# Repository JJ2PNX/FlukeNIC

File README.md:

# FlukeNIC - Fluke 884x Web Control & Logger Card

## Overview
The Fluke 884x is an outstanding multimeter.  
Even after 40+ years since its production, most units still function properly and maintain excellent accuracy.  
It's likely more reliable than many cheap modern benchtop meters.  
Its value increases when used in ways unique to benchtop instruments, beyond what handheld meters offer.  
GPIB was the traditional method, but a bit far from modern solution.  
I developed built-in web control and logger card that replaces the original GPIB board.  
NIC ... acronym of Network Interface Card.

---

## Features of This Card
- **WiFi Connectivity**
- **Web-based Control**
- **SD Card Stand-alone Logging**
- **Built-in, No modifications to the main unit required**

---

## How to Get

### 1. Hardware
Currently, no pre-assembled units or kits are available. Please build from the PCB.  
PCB fabrication files (UnitA/B.zip) are for JLCPCB.  
All necessary design materials are in the *hardware* directory.

### 2. Firmware
#### Method 1: Using ESP-IDF

1. Set up the ESP-IDF environment.
2. Clone the repository.
3. Refer to `firmware/README.md` for firmware download instructions.

#### Method 2: Using Flash Download Tool

1. Download **Flash Download Tool** from Espressif.  
   https://docs.espressif.com/projects/esp-test-tools/en/latest/esp32/production_stage/tools/flash_download_tool.html
2. Download `merge.bin` from the `firmware` directory to flash memory at address `0x0`.

---

## Help / How to Use

### 1. WiFi Connection
By default, FlukeNIC operates as a WiFi access point (AP).
- **SSID:** FlukeNIC  
- **Password:** 88408842  
- **IP Address:** 192.168.4.1  

You can configure WiFi Station settings by connecting to this AP, or by using the WPS push-button method.

#### WPS Push-Button Setup

1. Press the **SRQ** button repeatedly until the **SRQ** indicator lights.
2. When WPS succeeds, the **SRQ** indicator turns off and the **LISTEN** indicator turns on.

Settings are saved to flash memory, so the **LISTEN** indicator should light automatically upon the next power-on.

**Fluke Indicator Summary:**
| Indicator | Meaning |
|-----------|---------|
| SRQ | WiFi WPS Request |
| LISTEN | WiFi Associated |
| TALK | Logging is Active |ESP_ERROR_CHECK

---

### 2. Browser Access
Currently, only DHCP-assigned IPs are supported.  
In most cases, you can access it via:
http://flukenic.local/
If that doesn't work, check the DHCP-assigned IP address on your WiFi router.  
If you got the web interface, you probably won’t need further instructions!

---

### 3. Logging
microSD card is required.  
Start/stop operation can be performed using web-control or front panel **LOCAL** button.  
When logging is active, **TALK** indicator lights up.  
Results can be obtained using File Manager menu, or directly from microSD card, But hot swap is not supported.

---

### 4. Configuration
- Be sure to select the correct model (**8840 / 8842**).
- Other settings are optional.
- All configurations are saved to flash memory.

---

### 5. Troubleshooting
Communication with the Fluke unit is based on reverse-engineering and may malfunction with unexpected inputs.  
In such cases, use the **“Last bytes”** function in the Info menu to inspect the last communication log.  
Feel free to contact me — there may be a fix. Contributions are welcome!

---

### 6. Additional Notes
- SD card hot-swapping is not supported.  
Please insert or remove the card only when the power is off.
- BNC output is not implimented now.

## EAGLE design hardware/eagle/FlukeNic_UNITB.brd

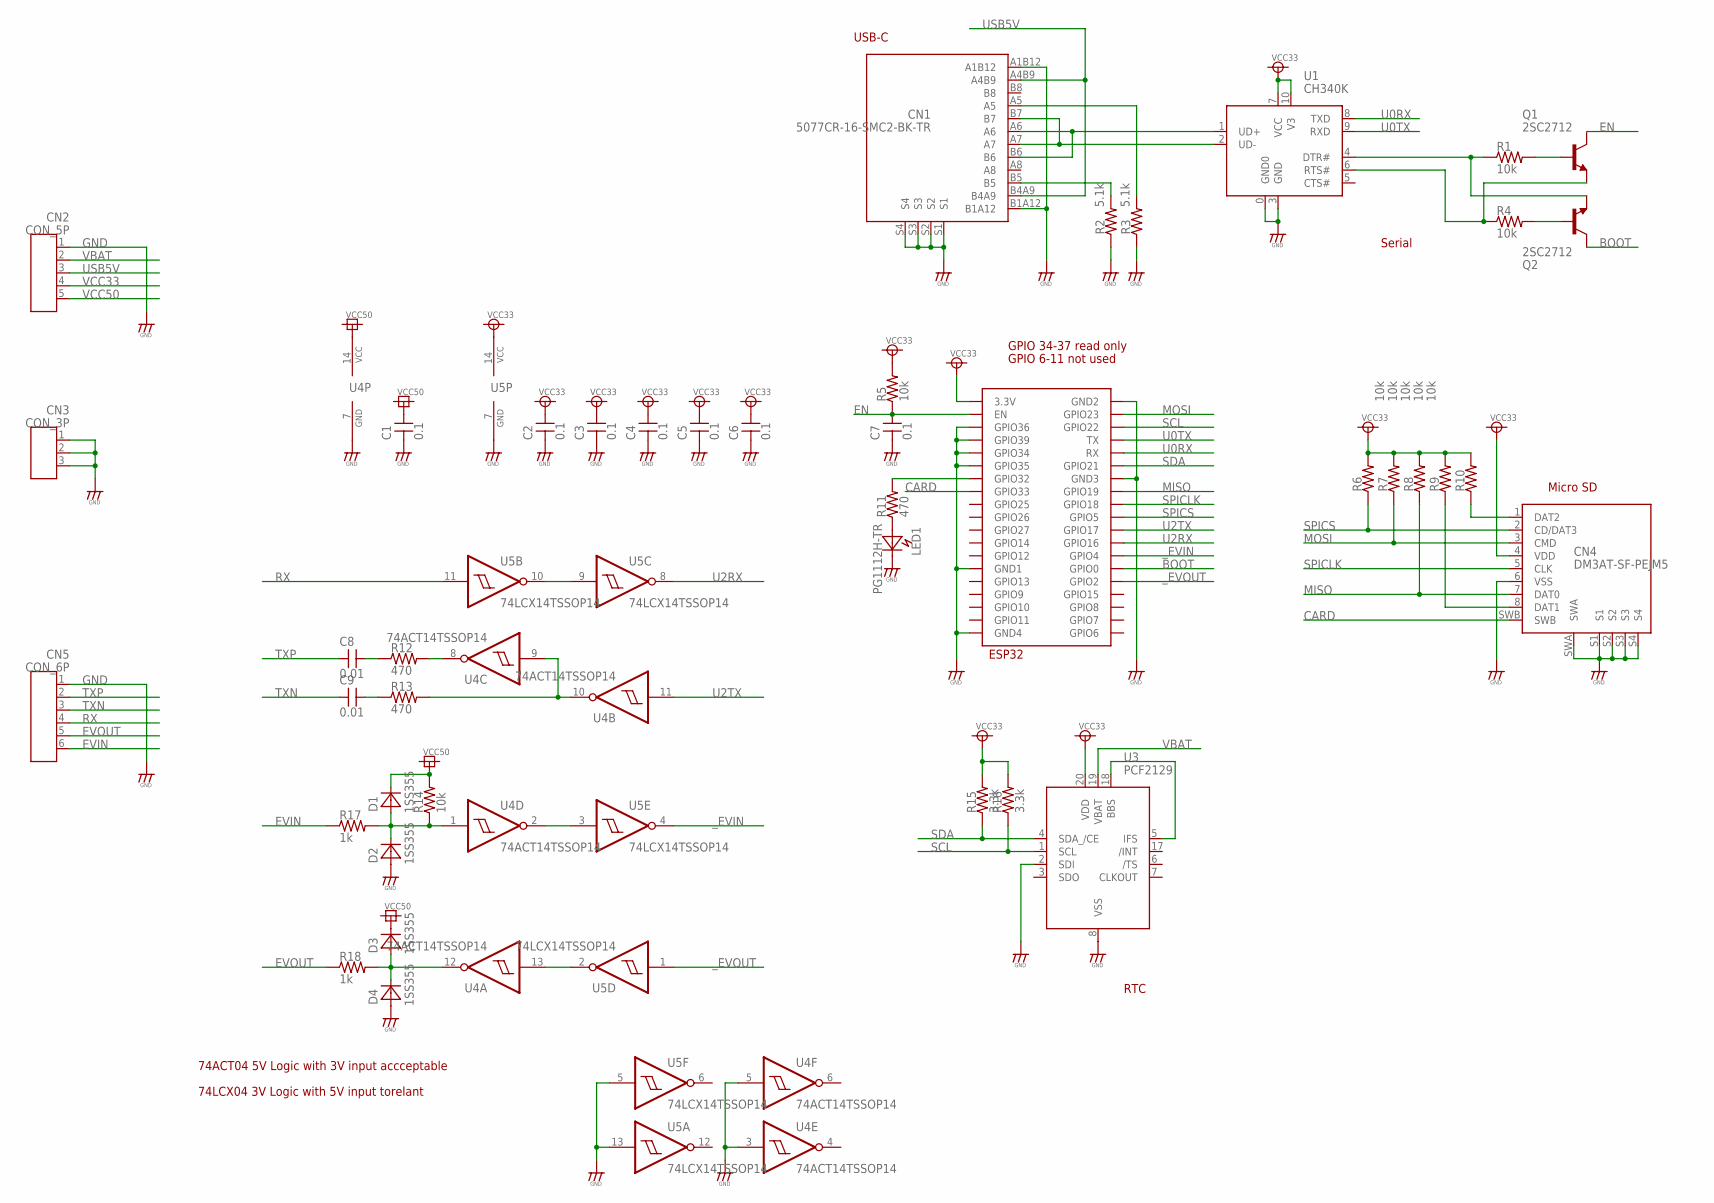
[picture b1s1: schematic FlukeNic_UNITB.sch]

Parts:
C1, C2, C3, C4, C5, C6, C7: 0.1; C2012
C8, C9: 0.01; C2012
CN1: 5077CR-16-SMC2-BK-TR
CN2: CON_5P; CON_HDR_SIP5
CN3: CON_3P; CON_HDR_SIP3
CN4: DM3AT-SF-PEJM5
CN5: CON_6P; CON_HDR_SIP6
D1, D2, D3, D4: 1SS355; SOD323
LED1: PG1112H-TR; LED2125
Q1, Q2: 2SC2712; SC59
R1, R4, R5, R6, R7, R8, R9, R10, R14: 10k; R2012
R2, R3: 5.1k; R2012
R11, R12, R13: 470; R2012
R15, R16: 3.3k; R2012
R17, R18: 1k; R2012
U1: CH340K; ESSOP10
U2: ESP32-WROOM
U3: PCF2129; SO20
U4: 74ACT14TSSOP14; TSSOP14
U5: 74LCX14TSSOP14; TSSOP14

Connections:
BBS: U3.5 (IFS), U3.18 (BBS)
BOOT: Q2.C, U2.IO0 (GPIO0)
CARD: CN4.SWB, U2.IO33 (GPIO33)
DAT1: CN4.8 (DAT1), R9.1
DAT2: CN4.1 (DAT2), R10.1
EN: C7.2, Q1.C, R5.1, U2.EN
EVIN: CN5.6, R17.1
EVOUT: CN5.5, R18.1
GND: C1.1, C2.1, C3.1, C4.1, C5.1, C6.1, C7.1, CN1.A1B12, CN1.B1A12, CN1.S1, CN1.S2, CN1.S3, CN1.S4, CN2.1, CN3.1, CN3.2, CN3.3, CN4.6 (VSS), CN4.S1, CN4.S2, CN4.S3, CN4.S4, CN4.SWA, CN5.1, D2.1 (A), D4.1 (A), LED1.K, R2.1, R3.1, U1.0 (GND0), U1.3 (GND), U2.GND1, U2.GND2, U2.GND3, U2.GND4, U2.IO34 (GPIO34), U2.IO35 (GPIO35), U2.SENSOR_VN (GPIO39), U2.SENSOR_VP (GPIO36), U3.2 (SDI), U3.8 (VSS), U4.3 (I), U4.5 (I), U4.7 (GND), U5.5 (I), U5.7 (GND), U5.13 (I)
MISO: CN4.7 (DAT0), R8.1, U2.IO19 (GPIO19)
MOSI: CN4.3 (CMD), R7.1, U2.IO23 (GPIO23)
unnamed: U4.13 (I), U5.2 (O)
unnamed: U4.2 (O), U5.3 (I)
unnamed: D1.1 (A), D2.2 (K), R14.1, R17.2, U4.1 (I)
unnamed: D3.1 (A), D4.2 (K), R18.2, U4.12 (O)
unnamed: R13.2, U4.9 (I), U4.10 (O)
unnamed: R12.2, U4.8 (O)
unnamed: U5.9 (I), U5.10 (O)
unnamed: C8.2, R12.1
unnamed: C9.2, R13.1
unnamed: LED1.A, R11.1
unnamed: Q1.B, R1.2
unnamed: Q2.B, R4.2
unnamed: CN1.B5, R2.2
unnamed: CN1.A5, R3.2
unnamed: Q2.E, R1.1, U1.4 (DTR#)
unnamed: Q1.E, R4.1, U1.6 (RTS#)
RX: CN5.4, U5.11 (I)
SCL: R16.1, U2.IO22 (GPIO22), U3.1 (SCL)
SDA: R15.1, U2.IO21 (GPIO21), U3.4 (SDA_/CE)
SPICLK: CN4.5 (CLK), U2.IO18 (GPIO18)
SPICS: CN4.2 (CD/DAT3), R6.1, U2.IO5 (GPIO5)
STATUS: R11.2, U2.IO32 (GPIO32)
TXN: C9.1, CN5.3
TXP: C8.1, CN5.2
U0RX: U1.8 (TXD), U2.RX
U0TX: U1.9 (RXD), U2.TX
U2RX: U2.IO16 (GPIO16), U5.8 (O)
U2TX: U2.IO17 (GPIO17), U4.11 (I)
UD+: CN1.A6, CN1.B6, U1.1 (UD+)
UD-: CN1.A7, CN1.B7, U1.2 (UD-)
USB5V: CN1.A4B9, CN1.B4A9, CN2.3
VBAT: CN2.2, U3.19 (VBAT)
VCC33: C2.2, C3.2, C4.2, C5.2, C6.2, CN2.4, CN4.4 (VDD), R5.2, R6.2, R7.2, R8.2, R9.2, R10.2, R15.2, R16.2, U1.7 (VCC), U1.10 (V3), U2.3V3 (3.3V), U3.20 (VDD), U5.14 (VCC)
VCC50: C1.2, CN2.5, D1.2 (K), D3.2 (K), R14.2, U4.14 (VCC)
_EVIN: U2.IO4 (GPIO4), U5.4 (O)
_EVOUT: U2.IO2 (GPIO2), U5.1 (I)

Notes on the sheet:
GPIO 6-11 not used
GPIO 34-37 read only
USB-C
Micro SD
RTC
Serial
74ACT04 5V Logic with 3V input accceptable
74LCX04 3V Logic with 5V input torelant

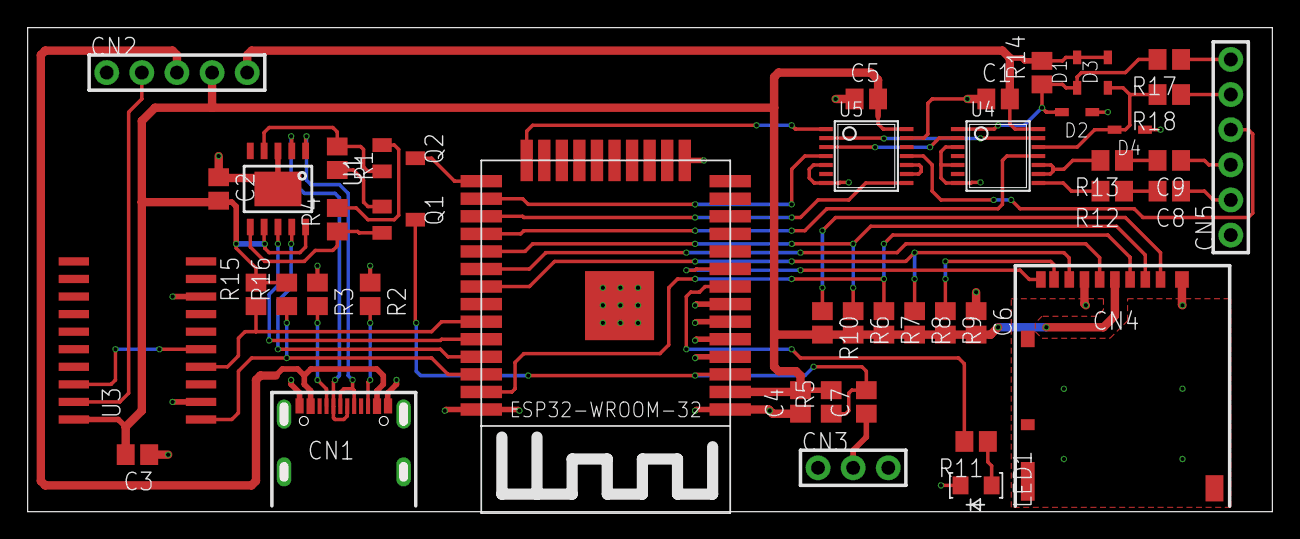
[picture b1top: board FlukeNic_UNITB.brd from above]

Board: 2 copper layers, 89.3 x 34.3 mm, 44 parts (0 on the bottom side), 47 nets.

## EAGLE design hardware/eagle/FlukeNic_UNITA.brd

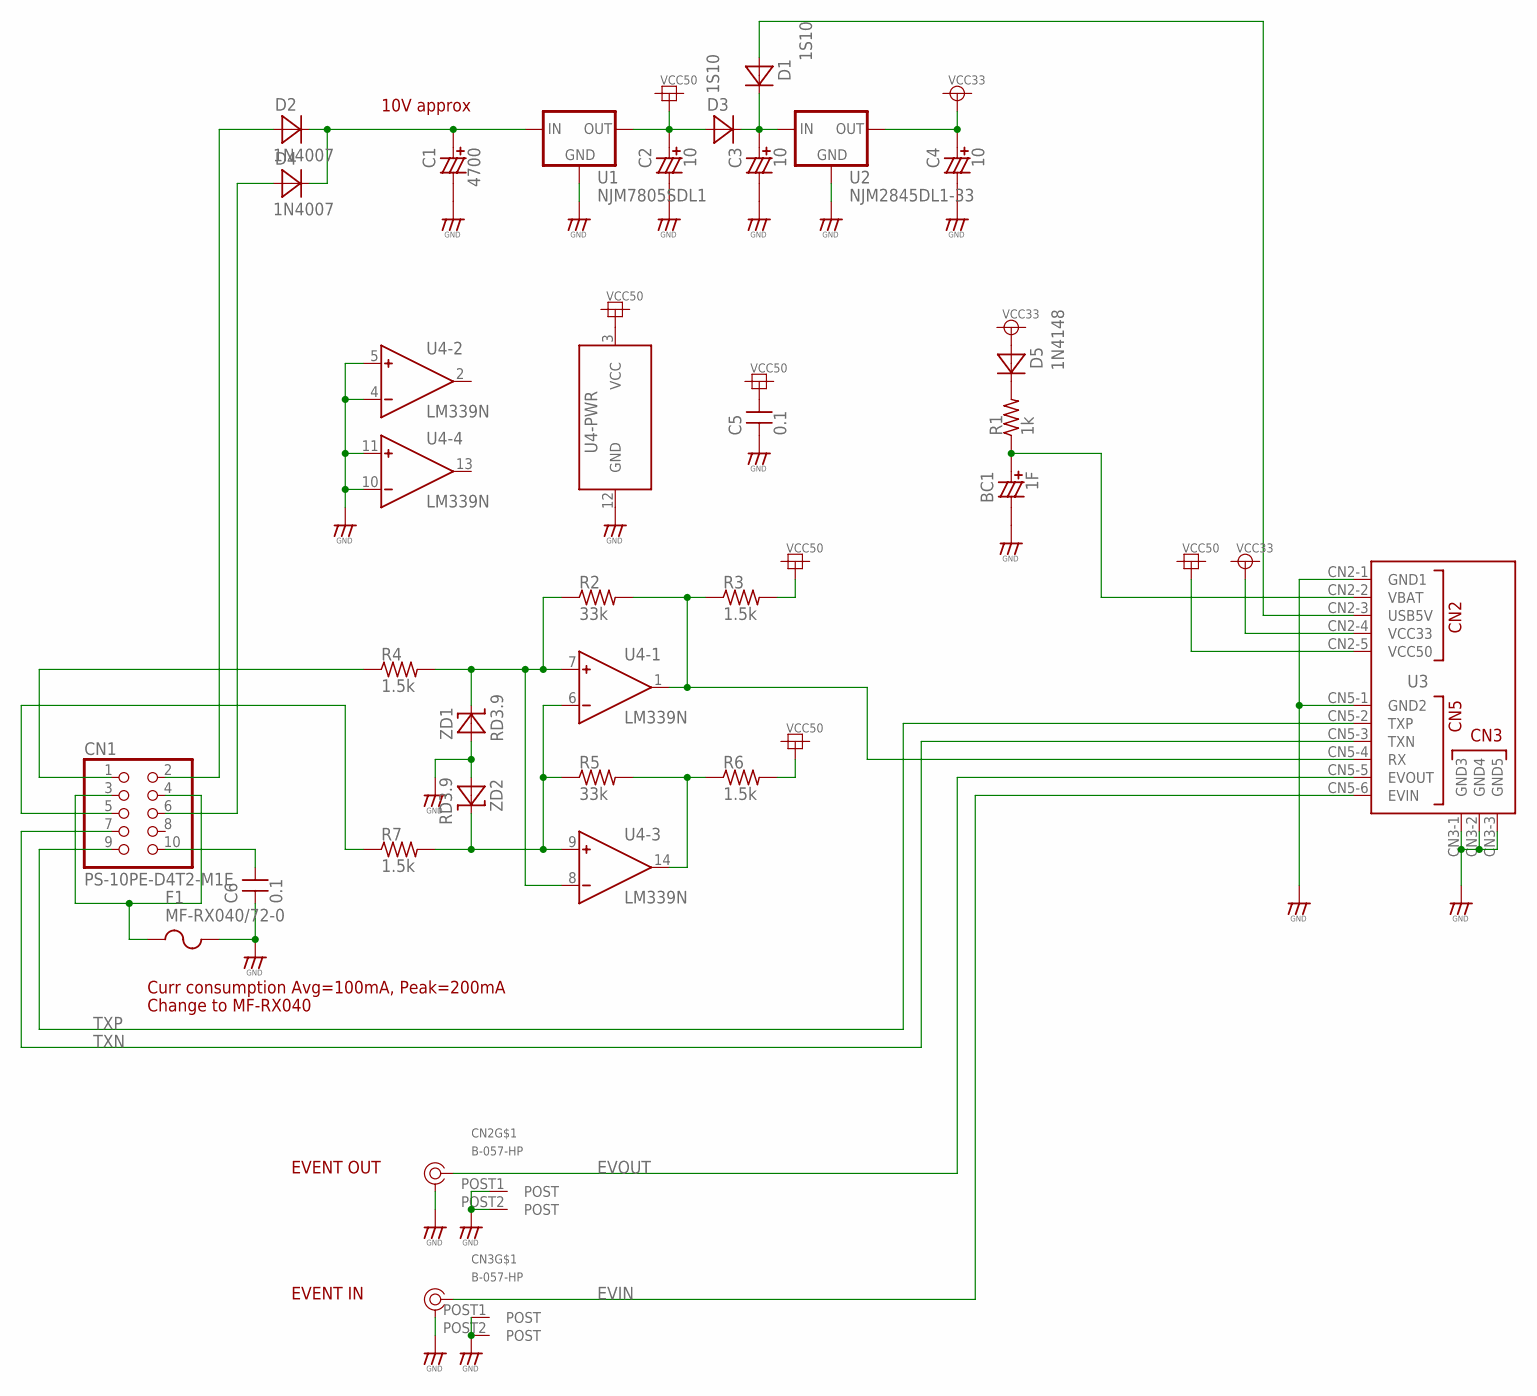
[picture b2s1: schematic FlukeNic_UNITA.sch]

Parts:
BC1: 1F; SE-5R5-D105VY
C1: 4700; CCAP_16
C2, C3, C4: 10; CCAP_6.5
C5, C6: 0.1; CAP_DIP_2
CN1: PS-10PE-D4T2-M1E
CN2, CN3: B-057-HP
D1, D3: 1S10; DIODE_4_1MM
D2, D4: 1N4007; DIODE_4_1MM
D5: 1N4148; DIODE_4
F1: MF-RX040/72-0; AX_08X02_2P_200
R1: 1k; R_0.25W_4
R2, R5: 33k; R_0.25W_4
R3, R4, R6, R7: 1.5k; R_0.25W_4
U1: NJM7805SDL1; TO252
U2: NJM2845DL1-33; TO252
U3: UNITB
U4: LM339N; DIL14
ZD1, ZD2: RD3.9; DIODE_4

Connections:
EVIN: CN3.HOT, U3.CN5-6 (EVIN)
EVOUT: CN2.HOT, U3.CN5-5 (EVOUT)
GND: BC1.-, C1.-, C2.-, C3.-, C4.-, C5.1, C6.1, CN2.COLD, CN2.POST1 (POST), CN2.POST2 (POST), CN3.COLD, CN3.POST1 (POST), CN3.POST2 (POST), F1.2, U1.2 (GND), U2.2 (GND), U3.CN2-1 (GND1), U3.CN3-1 (GND3), U3.CN3-2 (GND4), U3.CN3-3 (GND5), U3.CN5-1 (GND2), U4.4 (IN-), U4.5 (IN+), U4.10 (IN-), U4.11 (IN+), U4.12 (GND), ZD1.A, ZD2.A
unnamed: R2.1, R4.2, U4.7 (IN+), U4.8 (IN-), ZD1.K
unnamed: R5.1, R7.2, U4.6 (IN-), U4.9 (IN+), ZD2.K
unnamed: R5.2, R6.1, U4.14 (OUT)
unnamed: D5.K, R1.2
unnamed: CN1.3, CN1.4, F1.1
unnamed: C1.+, D2.K, D4.K, U1.1 (IN)
unnamed: CN1.2, D2.A
unnamed: CN1.6, D4.A
unnamed: C3.+, D1.K, D3.K, U2.1 (IN)
unnamed: C6.2, CN1.10
RX: R2.2, R3.1, U3.CN5-4 (RX), U4.1 (OUT)
RXN: CN1.5, R7.1
RXP: CN1.1, R4.1
TXN: CN1.7, U3.CN5-3 (TXN)
TXP: CN1.9, U3.CN5-2 (TXP)
USB5V: D1.A, U3.CN2-3 (USB5V)
VBAT: BC1.+, R1.1, U3.CN2-2 (VBAT)
VCC33: C4.+, D5.A, U2.3 (OUT), U3.CN2-4 (VCC33)
VCC50: C2.+, C5.2, D3.A, R3.2, R6.2, U1.3 (OUT), U3.CN2-5 (VCC50), U4.3 (VCC)

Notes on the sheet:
EVENT OUT
EVENT IN
10V approx
Curr consumption Avg=100mA, Peak=200mA
Change to MF-RX040

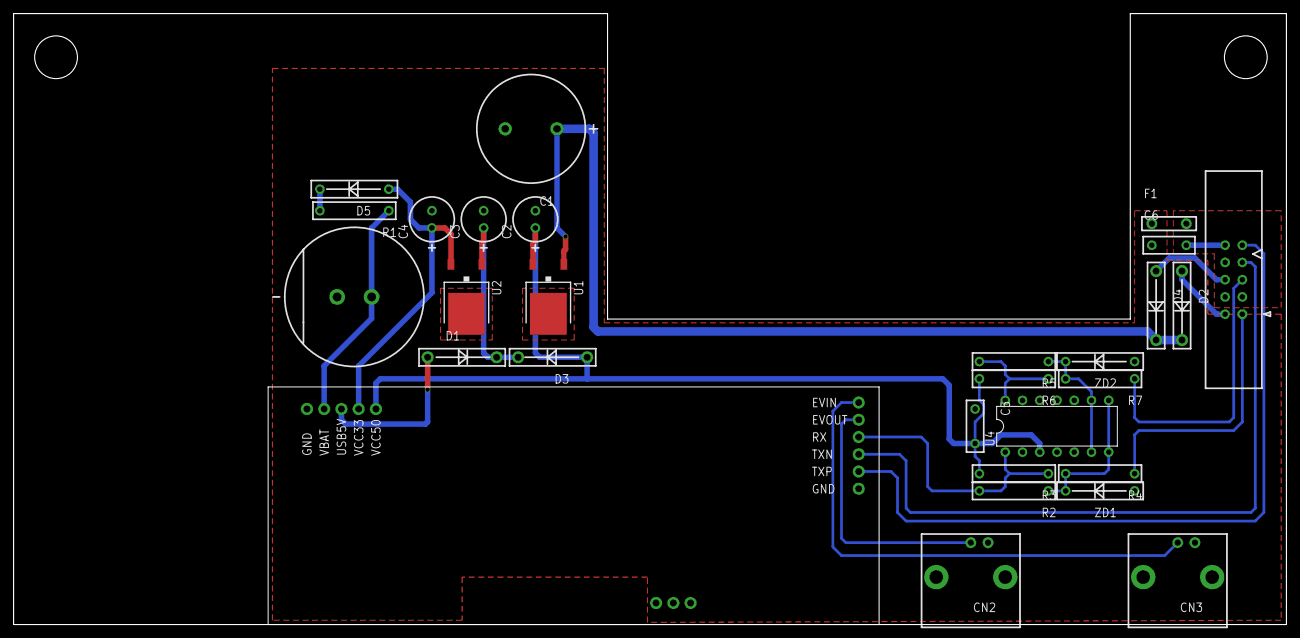
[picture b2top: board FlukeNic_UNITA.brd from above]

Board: 2 copper layers, 187.5 x 90.0 mm, 29 parts (0 on the bottom side), 22 nets.

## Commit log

2025-08-14 software 1st import
2025-08-18 fix not boot with brand-new pcf2129, change dir from software to firmware, append readme
2025-08-18 update readme, etc
2025-08-20 fix Makefile bin filename
2025-08-20 Add hardware
2025-08-20 Add firmware/README.md
2025-08-31 Add UDP data out, esp-idf esp32 chip info
2025-11-08 Add auxinfo range name, esp-idf ver 5.4.2 to 5.5.0 OTA using make ota URLPREFIX=http://hostname
2025-11-29 Added missing
2025-12-27 Add WiFi AP, Update README
2026-02-08 Change Fluke host I/O from 8-bit no parity to 7-bit odd parity, and improve stability. Add Wi-Fi TX power setting, Wi-Fi AP information, and IP address to the info page.
2026-02-21 Reduce localtime_r calls Standardize line endings to LF
2026-03-14 cleanup
2026-04-01 Fuse F1 not used, use jumper instead.
2026-04-01 Update BOM.xlsx, PartsLocation.pptx indicates F1 as jumper.
2026-04-12 Improve Wi-Fi reconnectivity
